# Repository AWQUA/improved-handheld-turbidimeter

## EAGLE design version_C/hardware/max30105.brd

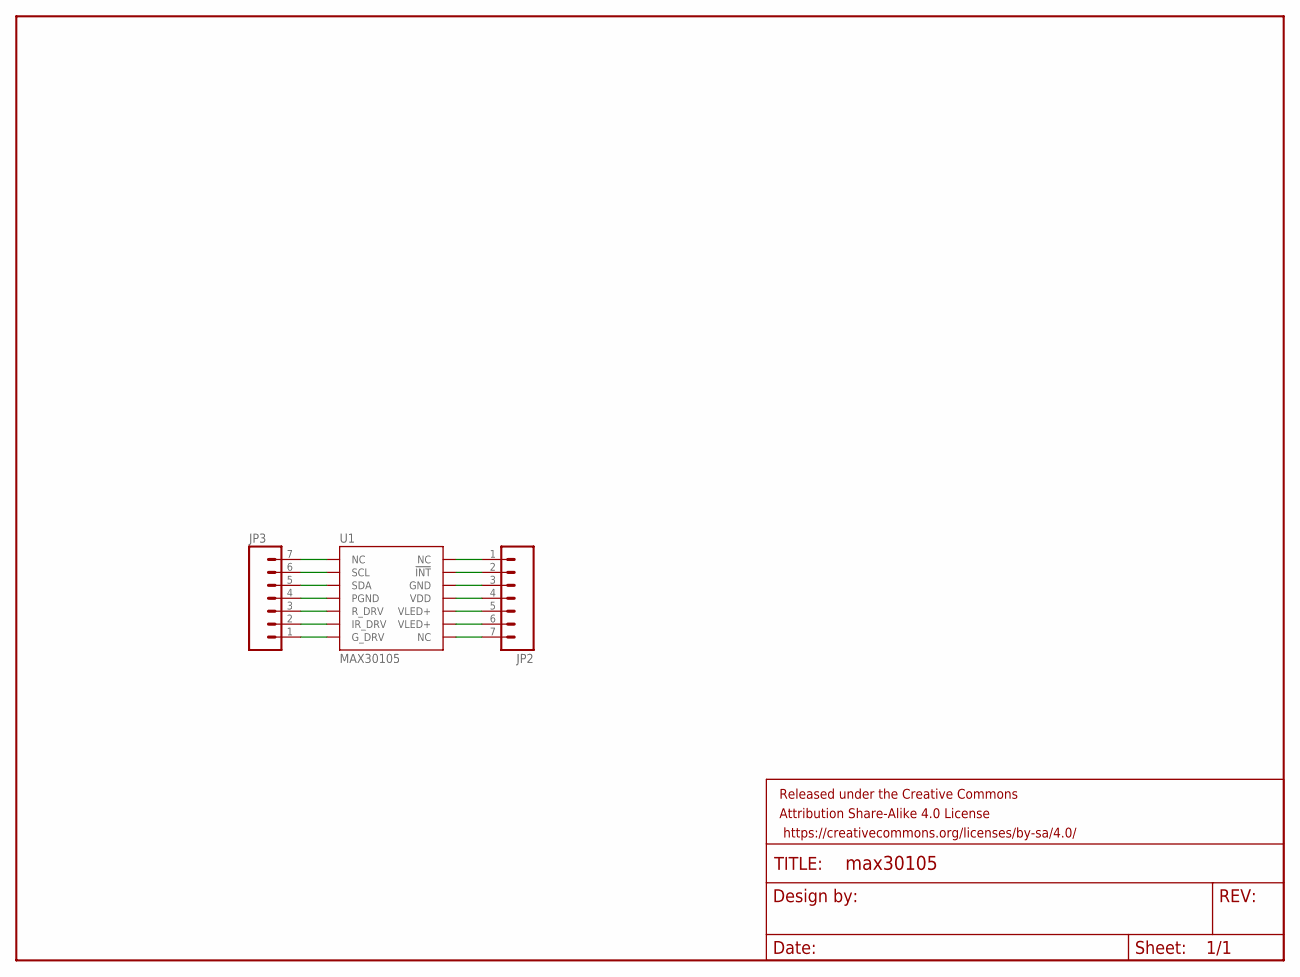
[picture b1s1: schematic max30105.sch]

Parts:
FRAME1: FRAME-LETTER; CREATIVE_COMMONS
JP2, JP3: M07; 1X07
U1: MAX30105; OLGA-14

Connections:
unnamed: JP2.1, U1.14 (NC)
unnamed: JP2.2, U1.13 (!INT)
unnamed: JP2.3, U1.12 (GND)
unnamed: JP2.4, U1.11 (VDD)
unnamed: JP2.5, U1.10 (VLED+)
unnamed: JP2.6, U1.9 (VLED+)
unnamed: JP2.7, U1.8 (NC)
unnamed: JP3.1, U1.7 (G_DRV)
unnamed: JP3.2, U1.6 (IR_DRV)
unnamed: JP3.3, U1.5 (R_DRV)
unnamed: JP3.4, U1.4 (PGND)
unnamed: JP3.5, U1.3 (SDA)
unnamed: JP3.6, U1.2 (SCL)
unnamed: JP3.7, U1.1 (NC)

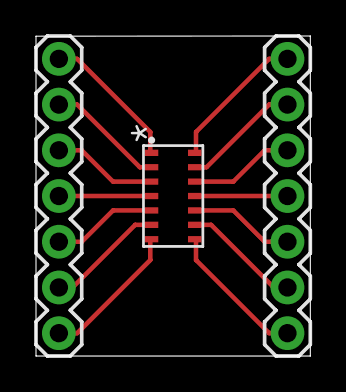
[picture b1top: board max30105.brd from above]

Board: 2 copper layers, 15.2 x 17.8 mm, 4 parts (0 on the bottom side), 14 nets.

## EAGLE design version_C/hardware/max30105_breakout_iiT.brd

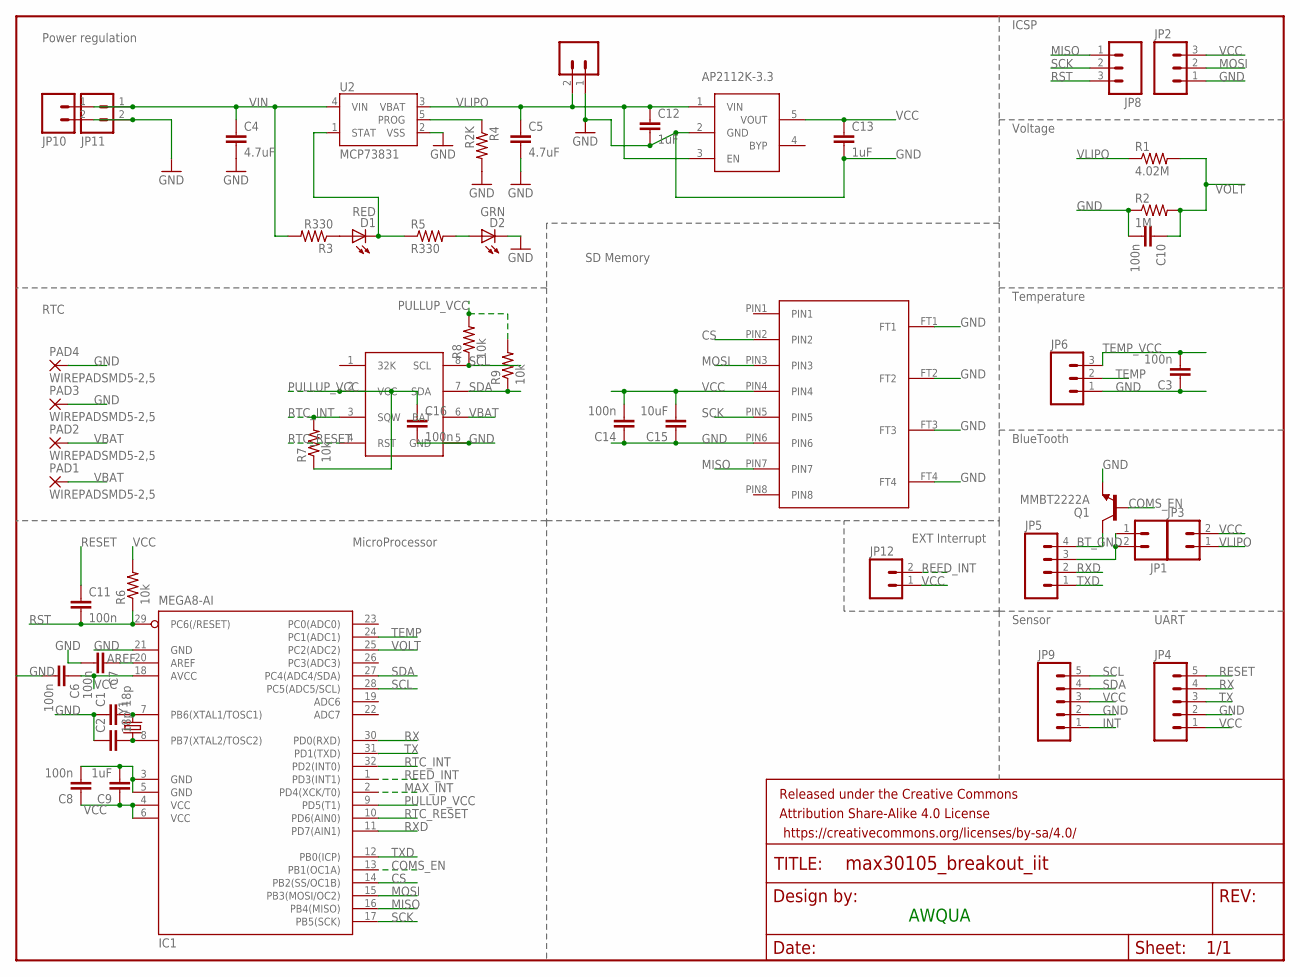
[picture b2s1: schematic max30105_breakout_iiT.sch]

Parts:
*RTC: DS3231M
C1, C2: 18p; 0603-CAP
C3, C6, C7, C8, C10, C11, C14, C16: 100n; 0603-CAP
C4, C5: 4.7uF; 0603-CAP
C9, C12, C13: 1uF; 0603-CAP
C15: 10uF; 0603-CAP
D1: RED; LED-0603
D2: GRN; LED-0603
FRAME1: FRAME-LETTER; CREATIVE_COMMONS
IC1: MEGA8-AI; TQFP32-08
JP1, JP3, JP10, JP11, JP12: M02PTH; 1X02
JP2, JP6, JP8: M03PTH; 1X03
JP4, JP9: M05PTH; 1X05
JP5: M04PTH; 1X04
JP7: LiPo Battery; JST-2-SMD
MICRO-SD: MICROSD-1010030368
PAD1, PAD2, PAD3, PAD4: WIREPADSMD5-2,5; 5-2,5
Q1: MMBT2222A; SOT23-3
R1: 4.02M; 0603-RES
R2: 1M; 0603-RES
R3, R5: R330; 0603-RES
R4: R2K; 0603-RES
R6, R7, R8, R9: 10k; 0603-RES
U2: MCP73831; SOT23-5
U$6: AP2112K-3.3; LP2985
Y1: CRYSTAL5X3; CRYSTAL-SMD-5X3

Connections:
AREF: C7.1, IC1.20 (AREF)
BT_GND: JP5.4, Q1.3 (C)
COMS_EN: IC1.13 (PB1(OC1A)), Q1.1 (B)
CS: IC1.14 (PB2(SS/OC1B)), MICRO-SD.PIN2
GND: *RTC.5 (GND), C1.1, C2.1, C3.1, C4.2, C5.2, C6.2, C7.2, C8.2, C9.2, C10.2, C12.2, C13.2, C14.1, C15.1, C16.2, D2.C, IC1.3 (GND), IC1.5 (GND), IC1.21 (GND), JP2.1, JP4.2, JP6.1, JP7.1, JP9.2, JP10.2, JP11.2, MICRO-SD.FT1, MICRO-SD.FT2, MICRO-SD.FT3, MICRO-SD.FT4, MICRO-SD.PIN6, PAD3.1, PAD4.1, Q1.2 (E), R2.1, R4.2, U2.2 (VSS), U$6.2 (GND)
INT: JP9.1
MAX_INT: IC1.2 (PD4(XCK/T0))
MISO: IC1.16 (PB4(MISO)), JP8.1, MICRO-SD.PIN7
MOSI: IC1.15 (PB3(MOSI/OC2)), JP2.2, MICRO-SD.PIN3
unnamed: D1.A, R3.1
unnamed: JP1.1, JP1.2, JP5.3
unnamed: D2.A, R5.2
PROG: R4.1, U2.5 (PROG)
PULLUP_VCC: *RTC.2 (VCC), C16.1, IC1.9 (PD5(T1)), R7.1, R8.2, R9.2
Q1: C2.2, IC1.8 (PB7(XTAL2/TOSC2)), Y1.1
Q2: C1.2, IC1.7 (PB6(XTAL1/TOSC1)), Y1.3 (2)
REED_INT: IC1.1 (PD3(INT1)), JP12.2
RESET: C11.1, JP4.5
RST: C11.2, IC1.29 (PC6(/RESET)), JP8.3, R6.1
RTC_INT: *RTC.3 (SQW), IC1.32 (PD2(INT0)), R7.2
RTC_RESET: *RTC.4 (RST), IC1.10 (PD6(AIN0))
RX: IC1.30 (PD0(RXD)), JP4.4
RXD: IC1.11 (PD7(AIN1)), JP5.2
SCK: IC1.17 (PB5(SCK)), JP8.2, MICRO-SD.PIN5
SCL: *RTC.8 (SCL), IC1.28 (PC5(ADC5/SCL)), JP9.5, R8.1
SDA: *RTC.7 (SDA), IC1.27 (PC4(ADC4/SDA)), JP9.4, R9.1
STAT: D1.C, R5.1, U2.1 (STAT)
TEMP: IC1.24 (PC1(ADC1)), JP6.2
TEMP_VCC: C3.2, JP6.3
TX: IC1.31 (PD1(TXD)), JP4.3
TXD: IC1.12 (PB0(ICP)), JP5.1
VBAT: *RTC.6 (BAT), PAD1.1, PAD2.1
VCC: C6.1, C8.1, C9.1, C13.1, C14.2, C15.2, IC1.4 (VCC), IC1.6 (VCC), IC1.18 (AVCC), JP2.3, JP3.2, JP4.1, JP9.3, JP12.1, MICRO-SD.PIN4, R6.2, U$6.5 (VOUT)
VIN: C4.1, JP10.1, JP11.1, R3.2, U2.4 (VIN)
VLIPO: C5.1, C12.1, JP3.1, JP7.2, R1.1, U2.3 (VBAT), U$6.1 (VIN), U$6.3 (EN)
VOLT: C10.1, IC1.25 (PC2(ADC2)), R1.2, R2.2

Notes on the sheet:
AWQUA
Temperature
UART
ICSP
Voltage
BlueTooth
Sensor
Power regulation
AP2112K-3.3
SD Memory
RTC
MicroProcessor
EXT Interrupt

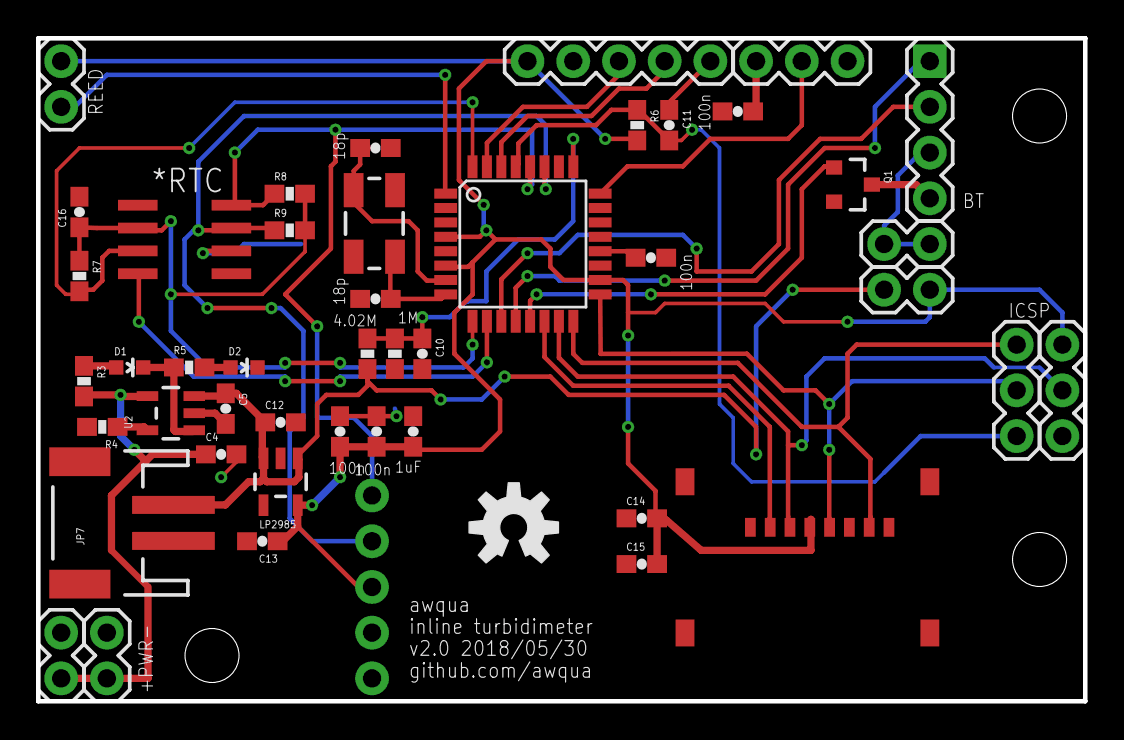
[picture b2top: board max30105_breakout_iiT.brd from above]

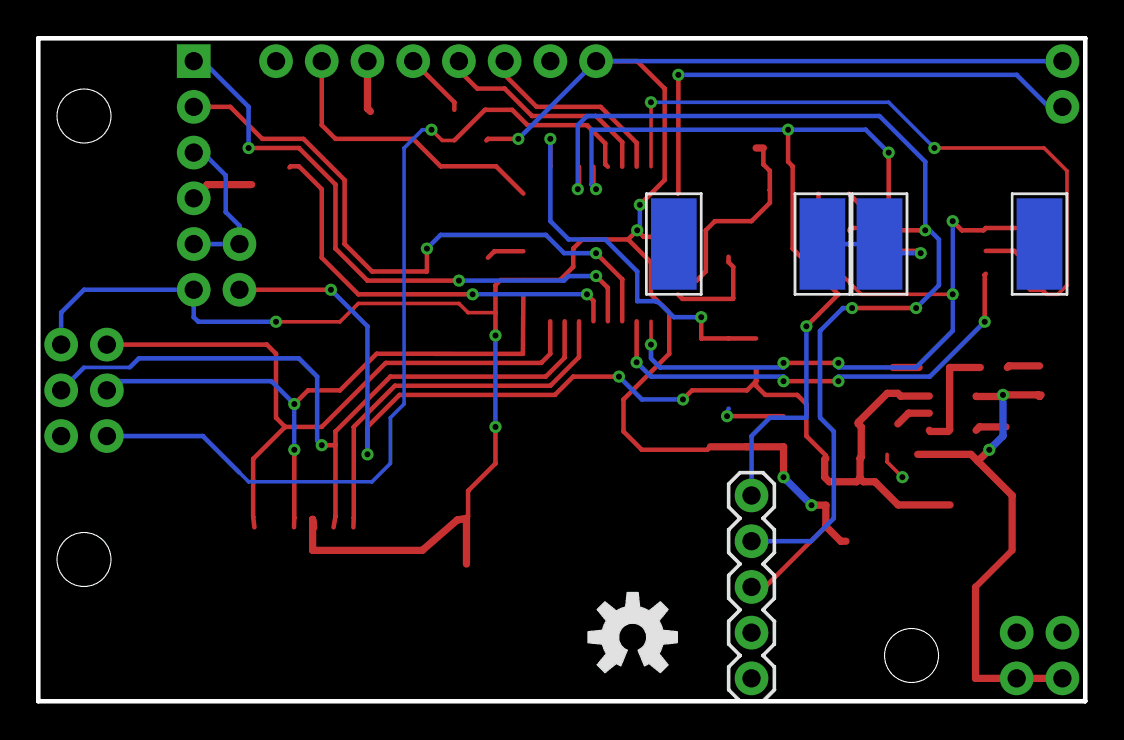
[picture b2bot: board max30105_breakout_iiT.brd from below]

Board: 2 copper layers, 58.2 x 36.8 mm, 53 parts (6 on the bottom side), 34 nets.

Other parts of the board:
U$1, U$4: OSHW-LOGO-M

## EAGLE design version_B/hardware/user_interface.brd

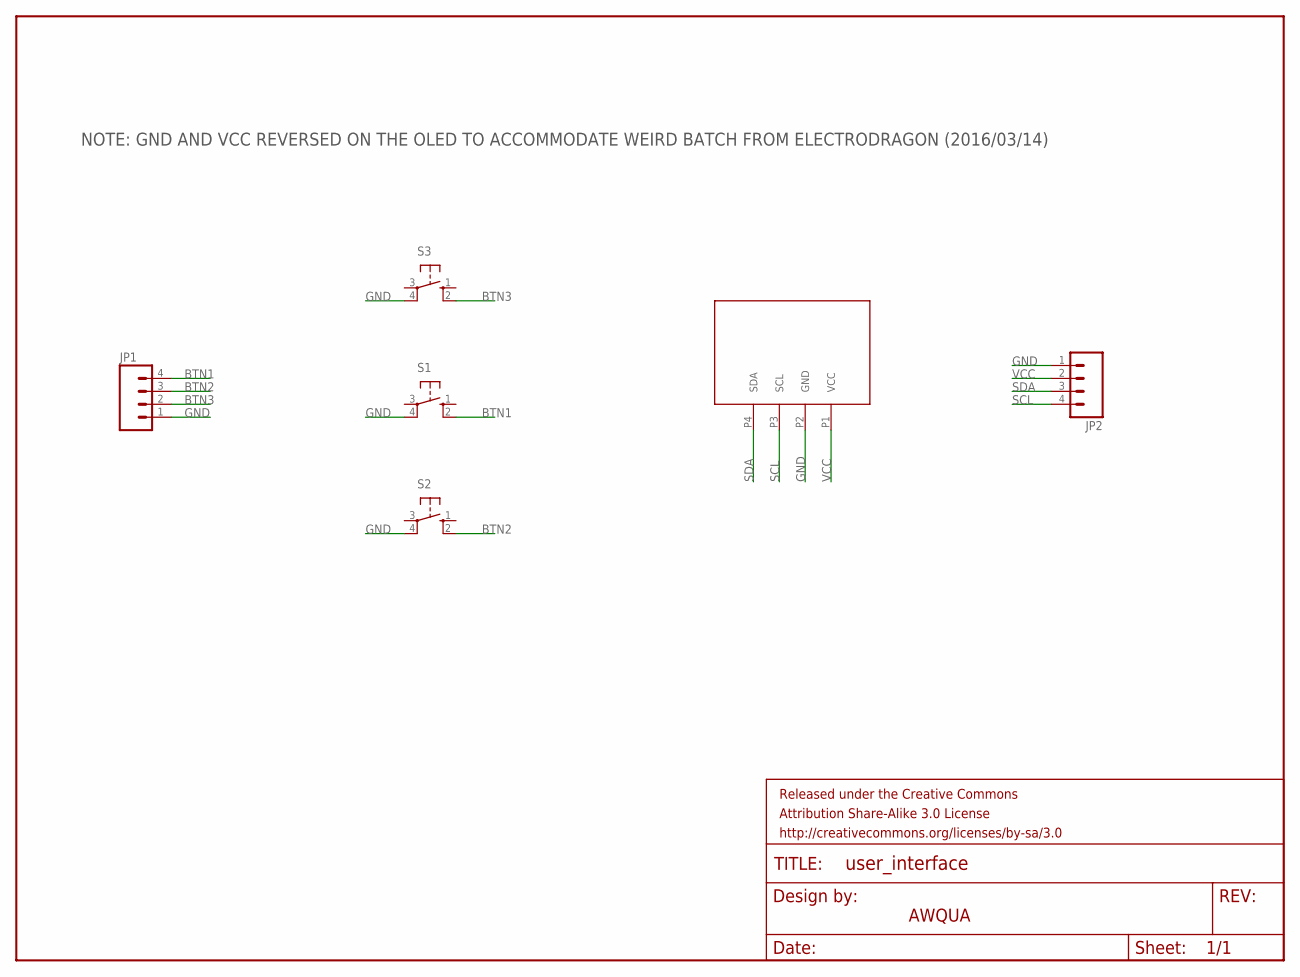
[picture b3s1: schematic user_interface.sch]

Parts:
FRAME1: FRAME-LETTER; CREATIVE_COMMONS
JP1, JP2: M04PTH; 1X04
S1, S2, S3: 40-XX; B3F-40XX
U$2: I2C-OLED-096

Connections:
BTN1: JP1.4, S1.2 (S1)
BTN2: JP1.3, S2.2 (S1)
BTN3: JP1.2, S3.2 (S1)
GND: JP1.1, JP2.1, S1.4 (P1), S2.4 (P1), S3.4 (P1), U$2.P2 (GND)
SCL: JP2.4, U$2.P3 (SCL)
SDA: JP2.3, U$2.P4 (SDA)
VCC: JP2.2, U$2.P1 (VCC)

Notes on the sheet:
AWQUA
NOTE: GND AND VCC REVERSED ON THE OLED TO ACCOMMODATE WEIRD BATCH FROM ELECTRODRAGON (2016/03/14)

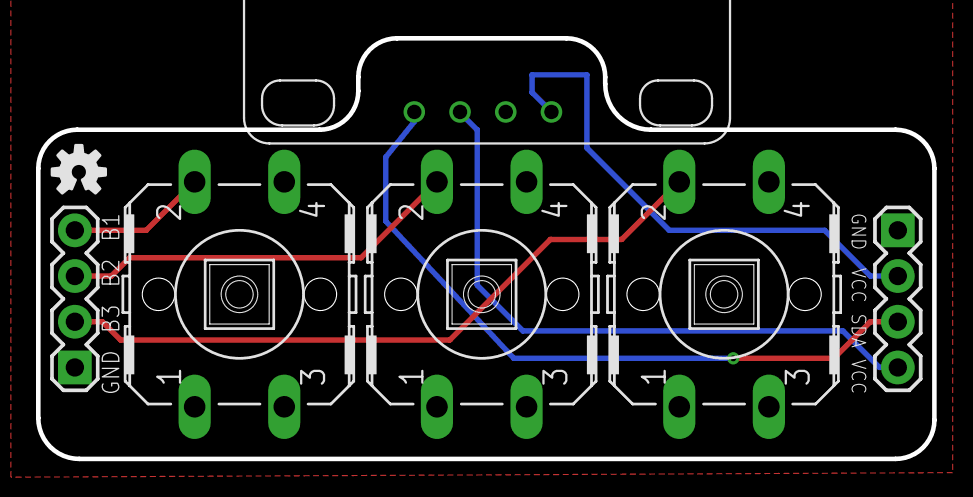
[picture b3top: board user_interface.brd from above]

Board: 2 copper layers, 49.8 x 23.4 mm, 9 parts (1 on the bottom side), 7 nets.

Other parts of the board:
U$1: OSHW-LOGO-S
U$4: OSHW-LOGO-M

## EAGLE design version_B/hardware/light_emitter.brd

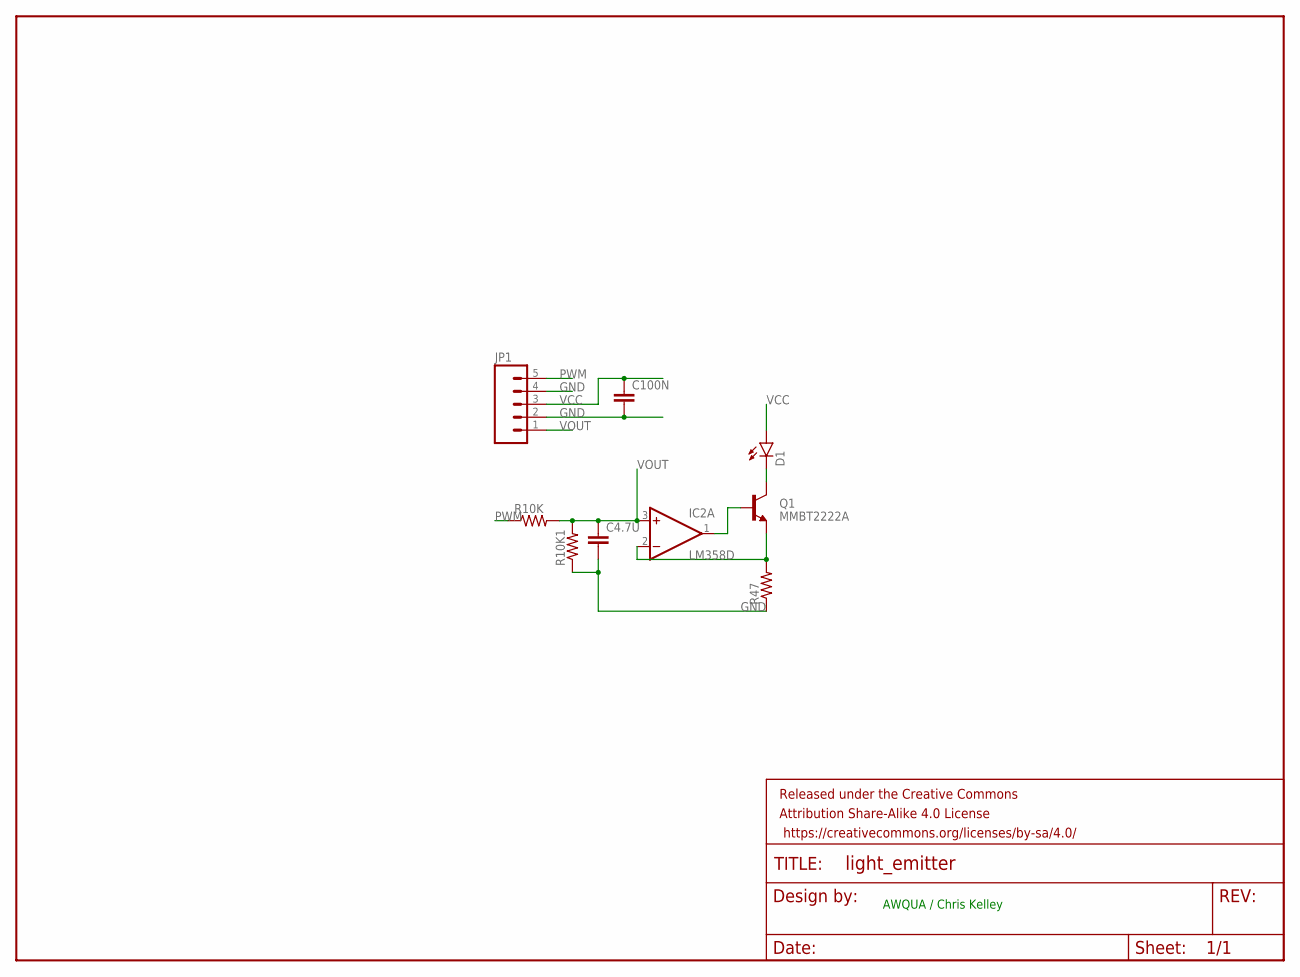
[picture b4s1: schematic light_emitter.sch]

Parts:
C4.7U, C100N: CAP0603-CAP; 0603-CAP
D1: LED5MM
FRAME1: FRAME-LETTER; CREATIVE_COMMONS
IC2: LM358D; SO08
JP1: M05PTH; 1X05
Q1: MMBT2222A; SOT23-3
R10K, R10K1, R47: RESISTOR0603-RES; 0603-RES

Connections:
GND: C4.7U.2, C100N.2, JP1.2, JP1.4, R10K1.1, R47.1
unnamed: IC2.2 (-IN), Q1.2 (E), R47.2
unnamed: IC2.1 (OUT), Q1.1 (B)
unnamed: D1.K (C), Q1.3 (C)
PWM: JP1.5, R10K.1
V+: IC2.8 (V+)
V-: IC2.4 (V-)
VCC: C100N.1, D1.A, JP1.3
VOUT: C4.7U.1, IC2.3 (+IN), JP1.1, R10K.2, R10K1.2

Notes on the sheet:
AWQUA / Chris Kelley

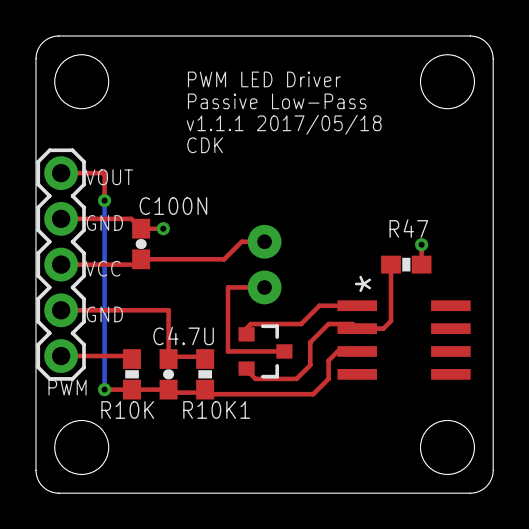
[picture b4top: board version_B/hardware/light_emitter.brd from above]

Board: 2 copper layers, 25.4 x 25.4 mm, 10 parts (1 on the bottom side), 7 nets.

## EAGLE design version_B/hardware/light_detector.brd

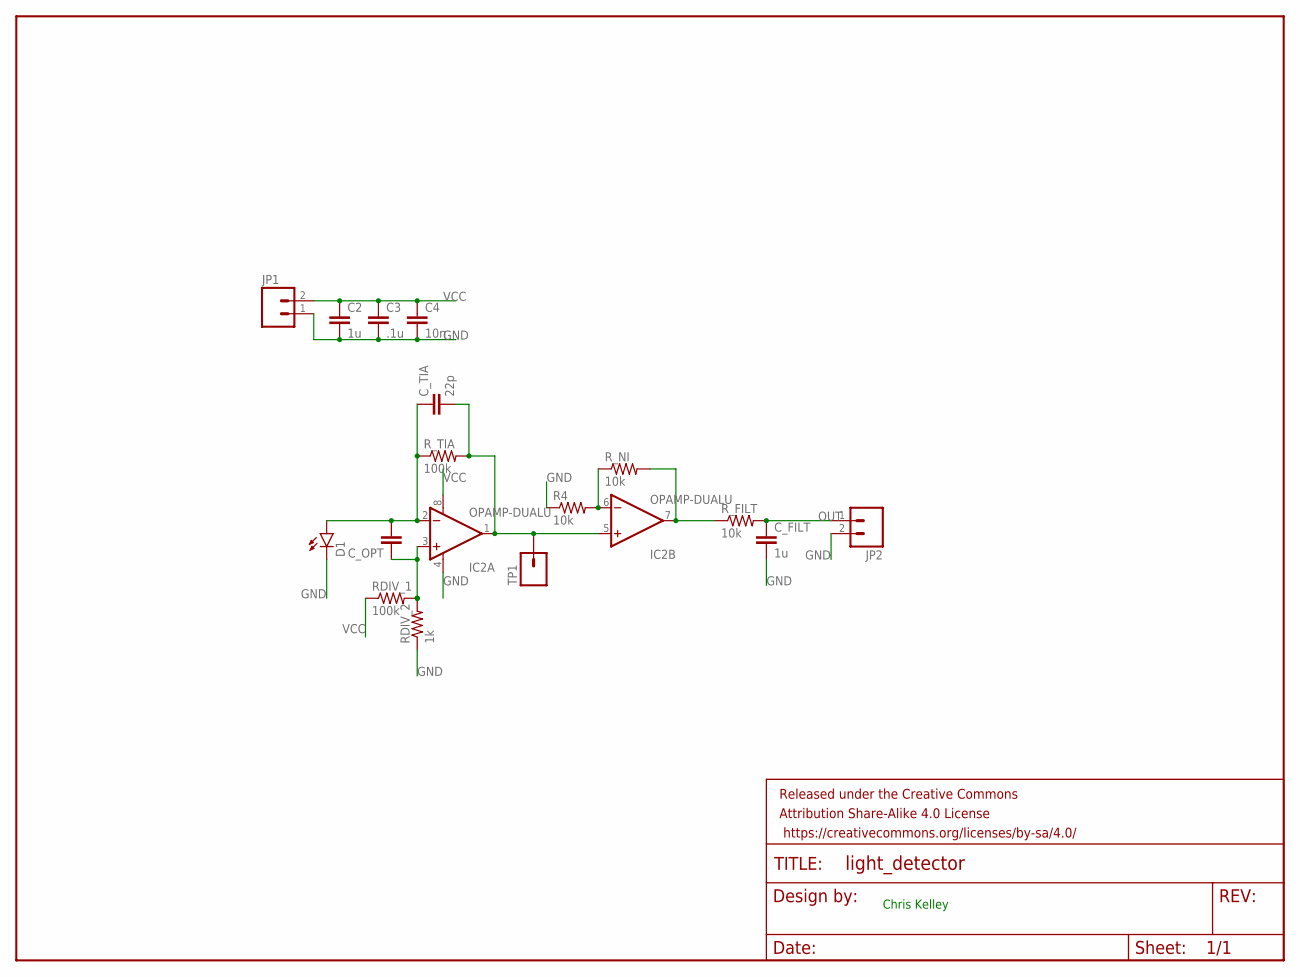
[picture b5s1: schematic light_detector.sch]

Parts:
C2: 1u; 0805
C3: .1u; 0805
C4: 10n; 0805
C_FILT: 1u; 0805
C_OPT: CAP0805; 0805
C_TIA: 22p; 0805
D1: LED5MM
FRAME1: FRAME-LETTER; CREATIVE_COMMONS
IC2: OPAMP-DUALU; SO08
JP1, JP2: M02PTH; 1X02
R4: 10k; 0603-RES
RDIV_1: 100k; 0603-RES
RDIV_2: 1k; 0603-RES
R_FILT: 10k; 0603-RES
R_NI: 10k; 0603-RES
R_TIA: 100k; 0603-RES
TP1: M01PTH; 1X01

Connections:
GND: C2.2, C3.2, C4.2, C_FILT.2, D1.K (C), IC2.4 (V-), JP1.1, JP2.2, R4.1, RDIV_2.1
unnamed: C_OPT.2, C_TIA.1, D1.A, IC2.2 (-IN), R_TIA.1
unnamed: C_TIA.2, IC2.1 (OUT), IC2.5 (+IN), R_TIA.2, TP1.1
unnamed: C_OPT.1, IC2.3 (+IN), RDIV_1.2, RDIV_2.2
unnamed: IC2.7 (OUT), R_FILT.1, R_NI.2
unnamed: IC2.6 (-IN), R4.2, R_NI.1
OUT: C_FILT.1, JP2.1, R_FILT.2
VCC: C2.1, C3.1, C4.1, IC2.8 (V+), JP1.2, RDIV_1.1

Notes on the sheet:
Chris Kelley

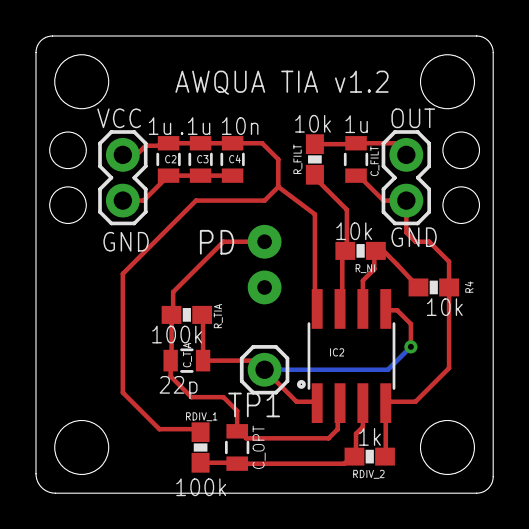
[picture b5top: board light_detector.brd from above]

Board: 2 copper layers, 25.4 x 25.4 mm, 18 parts (1 on the bottom side), 8 nets.

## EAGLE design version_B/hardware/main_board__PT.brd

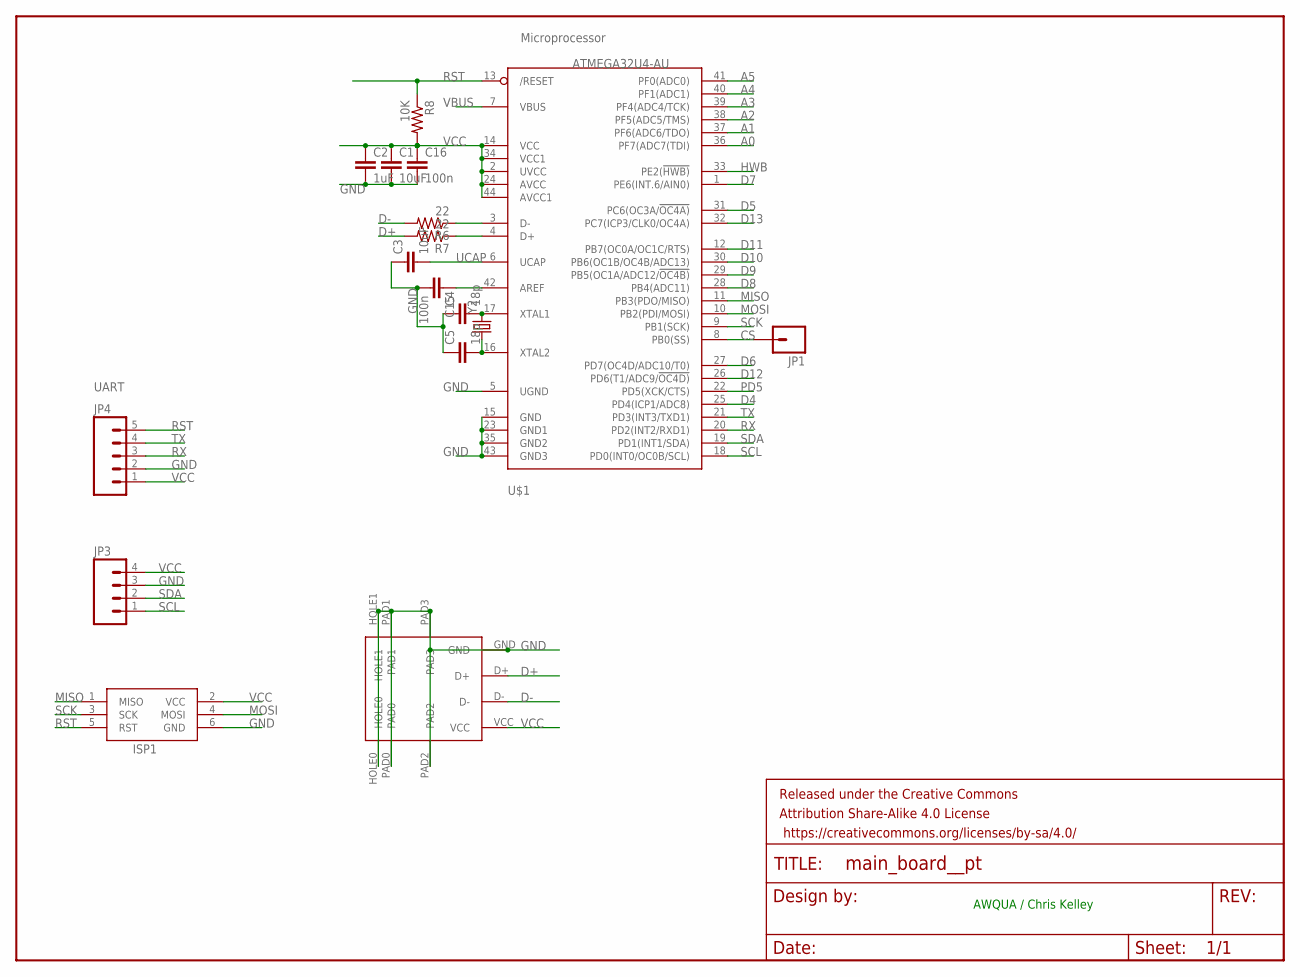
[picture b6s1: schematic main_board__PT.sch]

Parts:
C1, C3: 10uF; 0603-CAP
C2: 1uF; 0603-CAP
C4, C5: 18p; 0603-CAP
C15, C16: 100n; 0603-CAP
FRAME2: FRAME-LETTER; CREATIVE_COMMONS
ISP1: AVRISP-6; AVRISP
JP1: M01PTH; 1X01
JP3: M04PTH; 1X04
JP4: M05PTH; 1X05
R6, R7: 22; 0603-RES
R8: 10K; 1/6W-RES
U$1: ATMEGA32U4-AU; TQFP44
U$2: USBMICRO-10118193-0001LF
Y2: CRYSTAL5X3; CRYSTAL-SMD-5X3

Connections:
A0: U$1.36 (PF7(ADC7(TDI))
A1: U$1.37 (PF6(ADC6/TDO))
A2: U$1.38 (PF5(ADC5/TMS))
A3: U$1.39 (PF4(ADC4/TCK))
A4: U$1.40 (PF1(ADC1))
A5: U$1.41 (PF0(ADC0))
CS: JP1.1, U$1.8 (PB0(SS))
D4: U$1.25 (PD4(ICP1/ADC8))
D5: U$1.31 (PC6(OC3A/!OC4A))
D6: U$1.27 (PD7(OC4D/ADC10/T0))
D7: U$1.1 (PE6(INT.6/AIN0))
D8: U$1.28 (PB4(ADC11))
D9: U$1.29 (PB5(OC1A/ADC12/!OC4B))
D10: U$1.30 (PB6(OC1B/OC4B/ADC13))
D11: U$1.12 (PB7(OC0A/OC1C/RTS))
D12: U$1.26 (PD6(T1/ADC9/!OC4D))
D13: U$1.32 (PC7(ICP3/CLK0/OC4A))
D+: R7.2, U$2.D+
D-: R6.2, U$2.D-
GND: C1.2, C2.2, C3.1, C4.1, C5.1, C15.2, C16.2, ISP1.6 (GND), JP3.3, JP4.2, U$1.5 (UGND), U$1.15 (GND), U$1.23 (GND1), U$1.35 (GND2), U$1.43 (GND3), U$2.GND, U$2.HOLE0, U$2.HOLE1, U$2.PAD0, U$2.PAD1, U$2.PAD2, U$2.PAD3
HWB: U$1.33 (PE2(!HWB))
MISO: ISP1.1 (MISO), U$1.11 (PB3(PDO/MISO))
MOSI: ISP1.4 (MOSI), U$1.10 (PB2(PDI/MOSI))
unnamed: R6.1, U$1.3 (D-)
unnamed: R7.1, U$1.4 (D+)
unnamed: C15.1, U$1.42 (AREF)
unnamed: C4.2, U$1.17 (XTAL1), Y2.3 (2)
unnamed: C5.2, U$1.16 (XTAL2), Y2.1
PD5: U$1.22 (PD5(XCK/CTS))
RST: ISP1.5 (RST), JP4.5, R8.1, U$1.13 (/RESET)
RX: JP4.3, U$1.20 (PD2(INT2/RXD1))
SCK: ISP1.3 (SCK), U$1.9 (PB1(SCK))
SCL: JP3.1, U$1.18 (PD0(INT0/OC0B/SCL))
SDA: JP3.2, U$1.19 (PD1(INT1/SDA))
TX: JP4.4, U$1.21 (PD3(INT3/TXD1))
UCAP: C3.2, U$1.6 (UCAP)
VBUS: U$1.7 (VBUS)
VCC: C1.1, C2.1, C16.1, ISP1.2 (VCC), JP3.4, JP4.1, R8.2, U$1.2 (UVCC), U$1.14 (VCC), U$1.24 (AVCC), U$1.34 (VCC1), U$1.44 (AVCC1), U$2.VCC

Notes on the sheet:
UART
Microprocessor
AWQUA / Chris Kelley

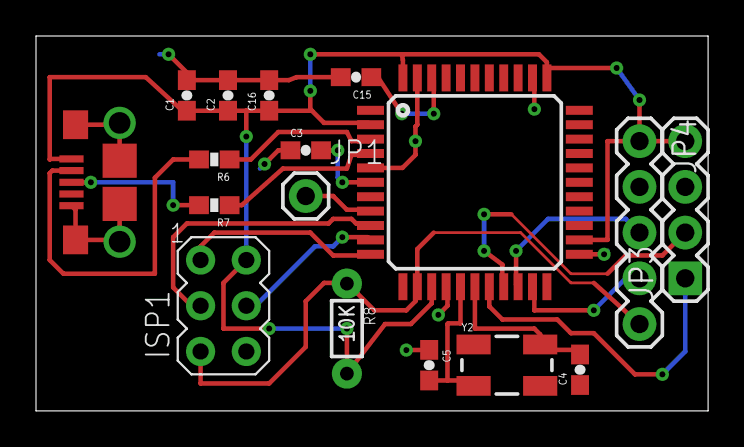
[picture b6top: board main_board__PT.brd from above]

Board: 2 copper layers, 37.3 x 20.8 mm, 18 parts (0 on the bottom side), 19 nets.

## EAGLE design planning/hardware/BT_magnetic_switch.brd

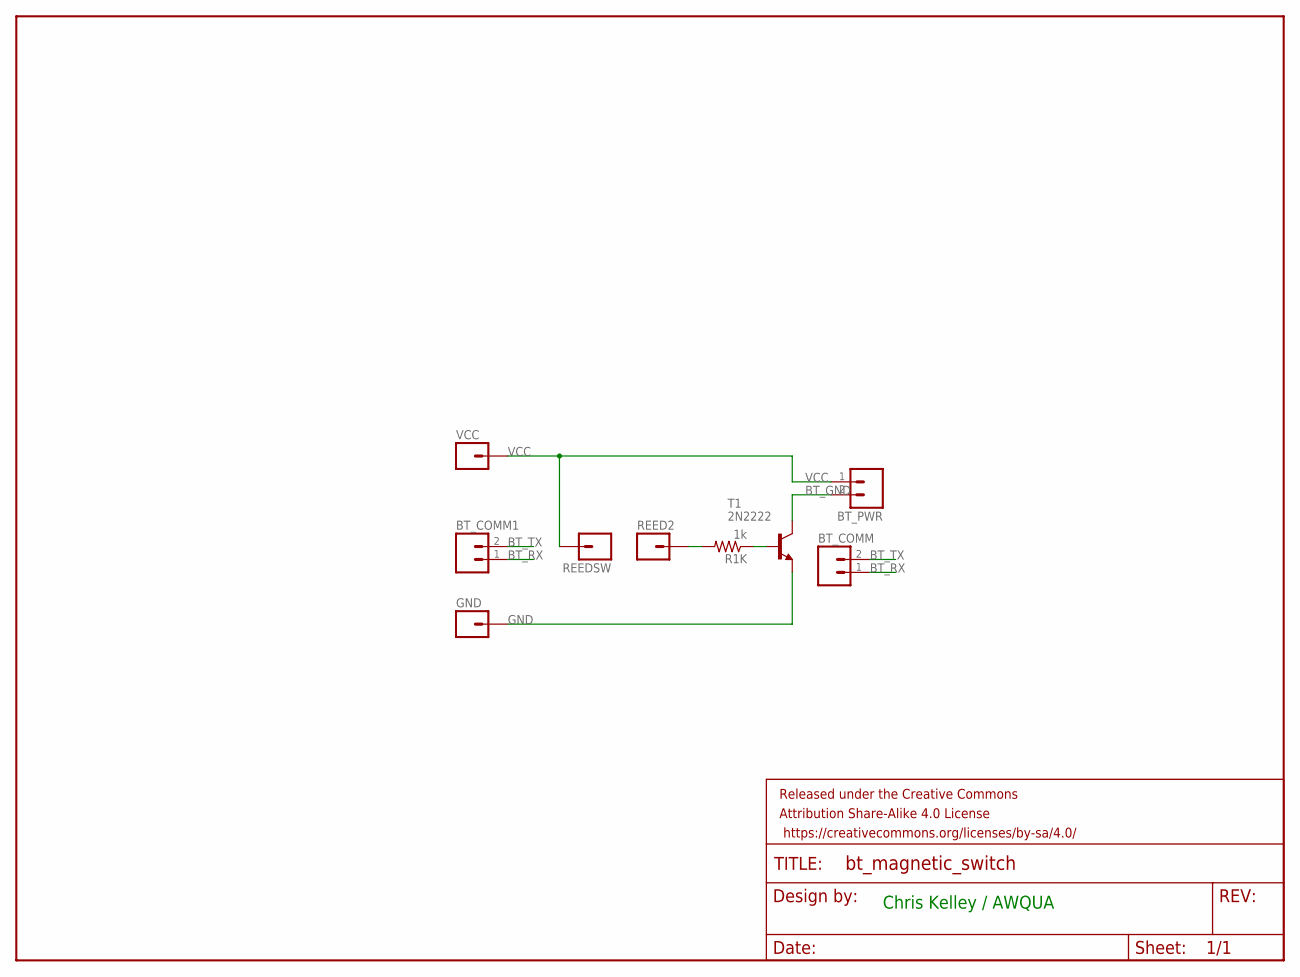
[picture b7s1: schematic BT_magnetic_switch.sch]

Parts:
BT_COMM, BT_COMM1: M02PTH; 1X02
BT_PWR: M02PTH; 1X02
FRAME1: FRAME-LETTER; CREATIVE_COMMONS
GND: M01PTH; 1X01
R1K: 1k; 0603-RES
REED2: M01PTH; 1X01
REEDSW: M01PTH; 1X01
T1: 2N2222; TO92-EBC-OVAL
VCC: M01PTH; 1X01

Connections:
BT_GND: BT_PWR.2, T1.C
BT_RX: BT_COMM.1, BT_COMM1.1
BT_TX: BT_COMM.2, BT_COMM1.2
GND: GND.1, T1.E
unnamed: R1K.1, T1.B
unnamed: R1K.2, REED2.1
VCC: BT_PWR.1, REEDSW.1, VCC.1

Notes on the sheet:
Chris Kelley / AWQUA

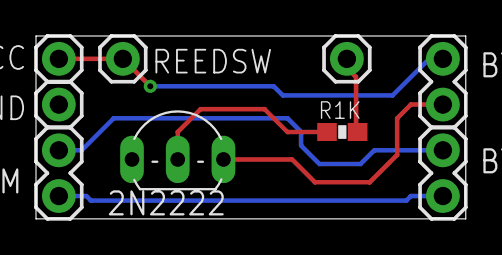
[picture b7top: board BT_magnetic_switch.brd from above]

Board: 2 copper layers, 23.9 x 10.2 mm, 10 parts (0 on the bottom side), 7 nets.

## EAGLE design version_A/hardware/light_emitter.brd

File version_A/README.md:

# improved-handheld-turbidimeter

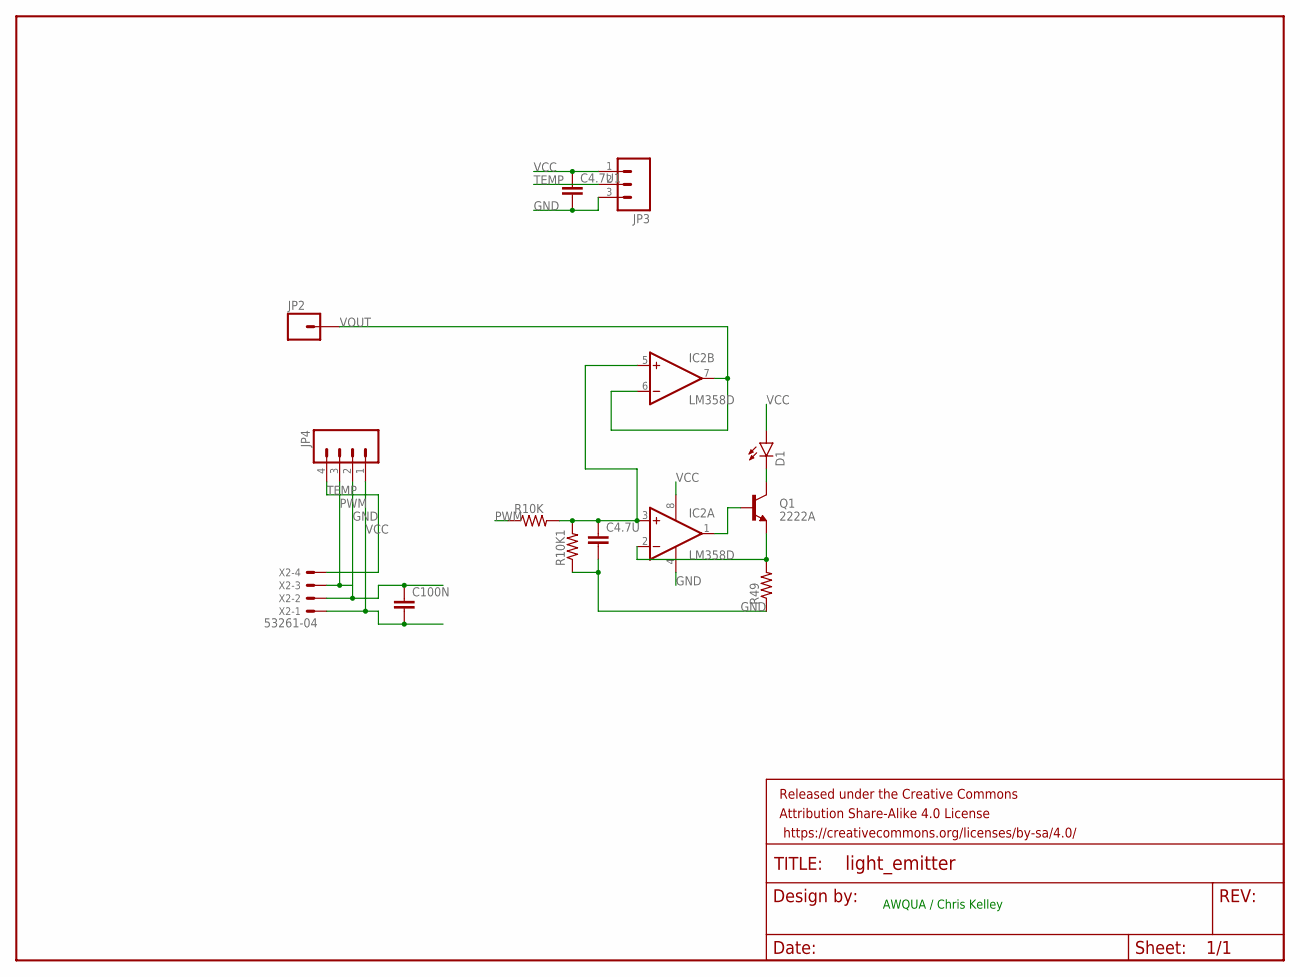
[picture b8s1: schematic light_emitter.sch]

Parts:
C4.7U, C4.7U1, C100N: CAP0603-CAP; 0603-CAP
D1: LED5MM
FRAME1: FRAME-LETTER; CREATIVE_COMMONS
IC2: LM358D; SO08
JP2: M01PTH; 1X01
JP3: M03PTH; 1X03
JP4: M04PTH; 1X04
Q1: 2222A; SOT23-3
R10K, R10K1, R49: RESISTOR0603-RES; 0603-RES
X2: 53261-04

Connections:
GND: C4.7U.2, C4.7U1.2, C100N.1, IC2.4 (V-), JP3.3, JP4.2, R10K1.1, R49.1, X2.2
unnamed: IC2.2 (-IN), Q1.2 (E), R49.2
unnamed: IC2.1 (OUT), Q1.1 (B)
unnamed: D1.K (C), Q1.3 (C)
PWM: JP4.3, R10K.1, X2.3
TEMP: JP3.2, JP4.4, X2.4
VCC: C4.7U1.1, C100N.2, D1.A, IC2.8 (V+), JP3.1, JP4.1, X2.1
VOUT: IC2.6 (-IN), IC2.7 (OUT), JP2.1
VOUT_PREBUF: C4.7U.1, IC2.3 (+IN), IC2.5 (+IN), R10K.2, R10K1.2

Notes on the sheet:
AWQUA / Chris Kelley

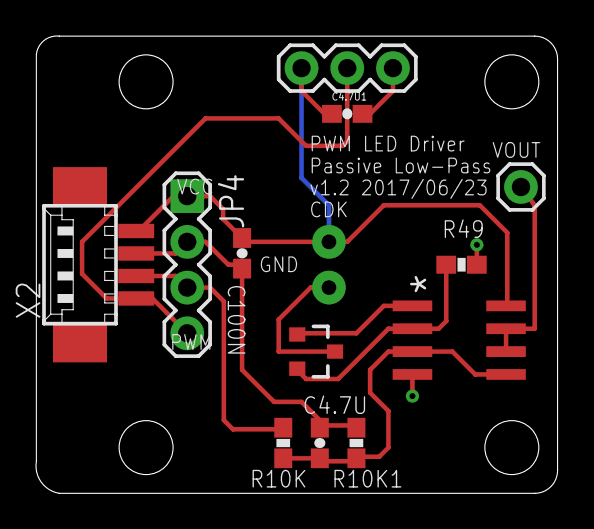
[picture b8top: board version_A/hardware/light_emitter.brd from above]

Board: 2 copper layers, 29.0 x 25.4 mm, 14 parts (1 on the bottom side), 9 nets.

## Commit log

2016-08-13 beginning migration from breadboard
2016-08-24 basic TIA board routed
2016-09-23 software and caseware updates
2016-11-02 updates to TIA
2016-11-02 new and updated component boards
2017-01-15 hardware update
2017-10-30 updates from local
2017-10-31 stencil files added for ALR demo board

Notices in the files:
parts and their libraries:
SparkFun-Passives: Licensing: Creative Commons ShareAlike 4.0 International - https://creativecommons.org/licenses/by-sa/4.0
SparkFun-Aesthetics: Released under the Creative Commons Attribution Share-Alike 4.0 License
SparkFun-Aesthetics: https://creativecommons.org/licenses/by-sa/4.0
